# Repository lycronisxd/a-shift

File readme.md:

# a-shift
## a high-quality sim racing shifter targeted at being as cheap as possible to manufacture.

\

### pcb and schematic

### bill of materials

﻿ Item No. | Part No. | Part Name | Qty. | Supplier | Unit Cost | Total Cost |
|---|---|---|---|---|---|---|
| 1 | 3D-001 | 3d printed y-axis chamber | 1 | 3d printing service / at home printing | N/A | N/A |
| 2 | 3D-002 | 3d printed x-axis bearing peg | 2 | 3d printing service / at home printing | N/A | N/A |
| 3 | 3D-003 | 3d printed y-axis bearing peg | 1 | 3d printing service / at home printing | N/A | N/A |
| 4 | 3D-004 | 3d printed main chassis | 1 | 3d printing service / at home printing | N/A | N/A |
| 5 | 3D-005 | 3d printed shift gate | 1 | 3d printing service / at home printing | N/A | N/A |
| 6 | 3D-006 | 3d printed y-axis bearing holder | 1 | 3d printing service / at home printing | N/A | N/A |
| 7 | 3D-007 | 3d printed shift knob | 1 | 3d printing service / at home printing | N/A | N/A |
| 8 | 3D-008 | 3d printed clamp head | 1 | 3d printing service / at home printing | N/A | N/A |
| 9 | 3D-009 | 3d printed clamp body | 1 | 3d printing service / at home printing | N/A | N/A |
| 10 | BR-001 | 608 series bearing | 4 | aliexpress | £0.44 | £4.35 (10pcs) |
| 11 | BR-002 | 625 series bearing | 2 | aliexpress | £0.37 | £3.68 (10pcs) |
| 12 | MNT-001 | m3x5mm bolt | 4 | accu | £0.27 | £1.08 |
| 13 | MNT-002 | m4 nut | 8 | accu | £0.18 | £1.44 |
| 14 | MNT-003 | m6 washers | 8 | accu | £0.19 | £1.52 |
| 15 | MNT-004 | m4x10mm bolt | 15 | accu | £0.15 | £2.25 |
| 16 | MNT-005 | m5 nut | 2 | accu | £0.43 | £0.86 |
| 17 | MNT-006 | m5x10mm bolt | 2 | accu | £0.49 | £0.98 |
| 18 | MNT-007 | m10 washer | 1 | accu | £0.82 | £0.82 |
| 19 | MNT-008 | m10 nut | 1 | accu | £1.01 | £1.01 |
| 20 | SPR-001 | 25mm long, 5mm diameter springs | 2 | aliexpress | £0.29 | £2.89 (10pcs) |
| 21 | SPR-002 | 45mm long, 5mm diameter springs | 2 | aliexpress | £0.37 | £3.73 (10pcs) |
| 22 | SPR-003 | 20mm long, 11mm diameter spring | 1 | aliexpress | £0.26 | £2.59 (10pcs) |
| 23 | MSC-001 | 200mm m10 threaded rod | 1 | aliexpress | £4.31 | £4.31 |
| 24 | MSC-002 | kw13-2 limit switches | 8 | aliexpress | £0.16 | £1.63 |
| 25 | PCB-001 | a-shift pcb (if assembled, ignore the following parts) | 1 | jlcpcb with gerber files | £4 | £4 |
| 26 | PCB-002 | CL21B105KBFNNNG 1uF capacitor | 1 | digikey | £0.09 | £0.09 |
| 27 | PCB-003 | CL21C220JBANNNC 22pF capacitor | 2 | digikey | £0.08 | £0.16 |
| 28 | PCB-004 | CL21B104KBCNNNC 0.1uF capacitor | 4 | digikey | £0.08 | £0.32 |
| 29 | PCB-005 | 1050170001 micro usb connector | 1 | digikey | £0.70 | £0.70 |
| 30 | PCB-006 | RC0805FR-0710KL 10k ohm resistor | 1 | digikey | £0.08 | £0.08 |
| 31 | PCB-007 | RC0805FR-0722RL 22 ohm resistor | 2 | digikey | £0.08 | £0.16 |
| 32 | PCB-008 | 1825910-6 tactile switch | 1 | digikey | £0.10 | £0.10 |
| 33 | PCB-009 | ATMEGA32U4-AU microcontroller | 1 | digikey | £4.01 | £4.01 |
| 34 | PCB-010 | ABM3-16.000MHZ-D2Y-T 16mhz crystal oscillator | 1 | digikey | £0.42 | £0.42 |\

total price (excl. 3d printing services, shipping and tax), <b>£43.18 (~60 USD)</b>

### relevant links
link to **public onshape project**:
<a href="https://cad.onshape.com/documents/ae479125a780254f271543a6/w/35b4ca05e55e778462ce5fb0/e/28c8145b059bf4585cd308b0"> click this </a>

link to **3d printed parts**:
<a href="https://www.thingiverse.com/thing:7376293">click here!</a>

### features
<ul>
<li>custom designed pcb based on the atmega32u4 for ease of future designing :)</li>
<li>7+R normally</li>
<li>5+R capability</li>
<li>sequential shifter capability</li>
<li>built in clamping system for tables or sim rigs</li>
</ul>

### how it works
<ul>
<li>uses a combination of software and hardware to be used as a shifter in racing or driving games</li>
<li>the used limit switches are mapped as controller buttons inside of game settings</li>
<li>can use the shifter sequentially if printing the sequential shift gate and using rubber bands!</li>
</ul>

### instructions
<a href="https://github.com/lycronisxd/a-shift/blob/main/instructions.md">click here!</a>

### credits + ai declaration
<a href="https://www.youtube.com/@amstudioprojects">amstudio</a> for <a href="https://www.youtube.com/watch?v=YMD8e26s7VE&t=88s">this video</a>\
about <a href="https://www.thingiverse.com/Noctiluxx/designs">noctiluxx's <a href="https://www.thingiverse.com/thing:1274947">h-pattern shifter design</a> for the forwards and backwards action of the shifter being locked <3 

i used google gemini to understand why the length of the shift lever mattered\
i used chatgpt to confirm the selection of the electronic components that i plan to use for the pcb (capacitors, resistors etc.)

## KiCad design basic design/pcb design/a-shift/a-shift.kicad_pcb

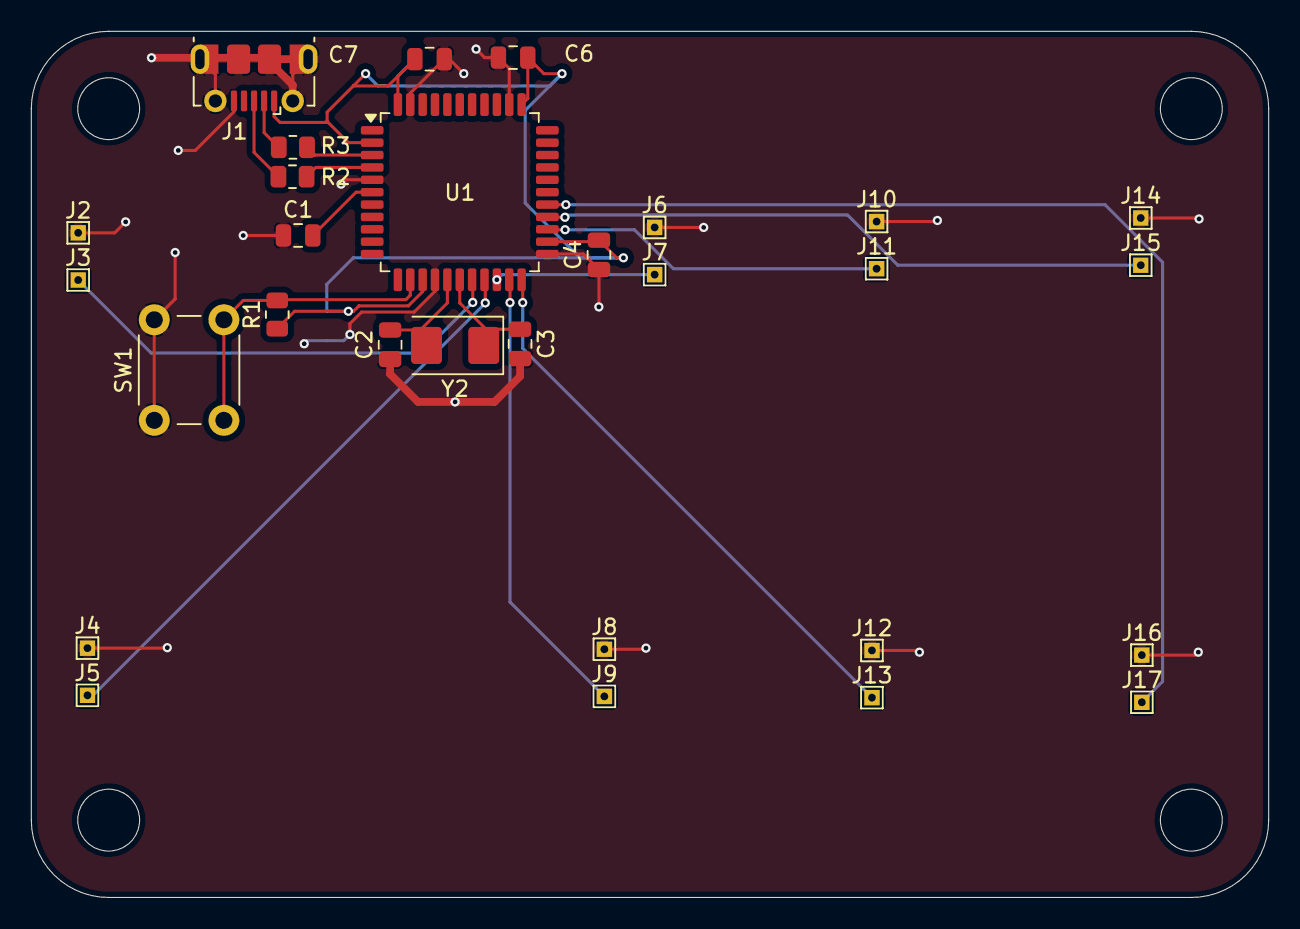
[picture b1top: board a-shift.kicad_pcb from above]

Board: 2 copper layers, 80.0 x 56.0 mm, 30 parts (1 on the bottom side), 18 nets.

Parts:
C1: 1uF; C_0805_2012Metric
C2, C3: 22pF; C_0805_2012Metric
C4, C5, C6, C7: 0.1uF; C_0805_2012Metric
J1: USB_B_Micro; USB_Micro-B_Molex-105017-0001
J2: GND1; TestPoint_THTPad_1.0x1.0mm_Drill0.5mm
J3: PD0; TestPoint_THTPad_1.0x1.0mm_Drill0.5mm
J4: GND2; TestPoint_THTPad_1.0x1.0mm_Drill0.5mm
J5: PD1; TestPoint_THTPad_1.0x1.0mm_Drill0.5mm
J6: GND3; TestPoint_THTPad_1.0x1.0mm_Drill0.5mm
J7: PD2; TestPoint_THTPad_1.0x1.0mm_Drill0.5mm
J8: GND4; TestPoint_THTPad_1.0x1.0mm_Drill0.5mm
J9: PD3; TestPoint_THTPad_1.0x1.0mm_Drill0.5mm
J10: GND5; TestPoint_THTPad_1.0x1.0mm_Drill0.5mm
J11: PD4; TestPoint_THTPad_1.0x1.0mm_Drill0.5mm
J12: GND6; TestPoint_THTPad_1.0x1.0mm_Drill0.5mm
J13: PD5; TestPoint_THTPad_1.0x1.0mm_Drill0.5mm
J14: GND7; TestPoint_THTPad_1.0x1.0mm_Drill0.5mm
J15: PD6; TestPoint_THTPad_1.0x1.0mm_Drill0.5mm
J16: GND8; TestPoint_THTPad_1.0x1.0mm_Drill0.5mm
J17: PD7; TestPoint_THTPad_1.0x1.0mm_Drill0.5mm
R1: 10k; R_0805_2012Metric
R2, R3: 22; R_0805_2012Metric
SW1: SW_Push; SW_PUSH_6mm
U1: ATmega32U4-A; TQFP-44_10x10mm_P0.8mm
Y2: Crystal_GND3_Small; Crystal_SMD_5032-2Pin_5.0x3.2mm

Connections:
+5V: C4.2, C5.2, C6.2, C7.2, J1.1 (VBUS), R1.1, U1.2 (UVCC), U1.14 (VCC), U1.24 (AVCC), U1.34 (VCC), U1.44 (AVCC)
/PD0: J3.1 (Pin_1_1), U1.18 (PD0)
/PD1: J5.1 (Pin_1_1), U1.19 (PD1)
/PD2: J7.1 (Pin_1_1), U1.20 (PD2)
/PD3: J9.1 (Pin_1_1), U1.21 (PD3)
/PD4: J11.1 (Pin_1_1), U1.25 (PD4)
/PD5: J13.1 (Pin_1_1), U1.22 (PD5)
/PD6: J15.1 (Pin_1_1), U1.26 (PD6)
/PD7: J17.1 (Pin_1_1), U1.27 (PD7)
/d+: J1.3 (D+), R2.1
/d-: J1.2 (D-), R3.1
GND: C1.1, C2.1, C3.2, C4.1, C5.1, C6.1, C7.1, J1.5 (GND), J1.SH (Shield), J2.1 (Pin_1_1), J4.1 (Pin_1_1), J6.1 (Pin_1_1), J8.1 (Pin_1_1), J10.1 (Pin_1_1), J12.1 (Pin_1_1), J14.1 (Pin_1_1), J16.1 (Pin_1_1), SW1.1, U1.5 (UGND), U1.15 (GND), U1.23 (GND), U1.35 (GND), U1.43 (GND)
unnamed: R2.2, U1.4 (D+)
unnamed: R3.2, U1.3 (D-)
unnamed: C1.2, U1.6 (UCAP)
unnamed: C3.1, U1.17 (XTAL1), Y2.1
unnamed: C2.2, U1.16 (XTAL2), Y2.2
unnamed: R1.2, SW1.2, U1.13 (~RESET)

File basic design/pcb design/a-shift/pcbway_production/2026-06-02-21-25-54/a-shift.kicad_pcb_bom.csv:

Designator,Quantity,Value,Footprint,Package,MPN,DNP,Mount_Type,Description,KiLib_Generator
C1,1,1uF,C_0805_2012Metric,,,,smt,"Unpolarized capacitor, small symbol",SMD_2terminal_chip_molded
"C2, C3",2,22pF,C_0805_2012Metric,,,,smt,"Unpolarized capacitor, small symbol",SMD_2terminal_chip_molded
"C4, C5, C6, C7",4,0.1uF,C_0805_2012Metric,,,,smt,"Unpolarized capacitor, small symbol",SMD_2terminal_chip_molded
J1,1,USB_B_Micro,USB_Micro-B_Molex-105017-0001,,,,smt,USB Micro Type B connector,
J10,1,GND5,TestPoint_THTPad_1.0x1.0mm_Drill0.5mm,,,,tht,"Generic connector, single row, 01x01, script generated (kicad-library-utils/schlib/autogen/connector/)",
J11,1,PD4,TestPoint_THTPad_1.0x1.0mm_Drill0.5mm,,,,tht,"Generic connector, single row, 01x01, script generated (kicad-library-utils/schlib/autogen/connector/)",
J12,1,GND6,TestPoint_THTPad_1.0x1.0mm_Drill0.5mm,,,,tht,"Generic connector, single row, 01x01, script generated (kicad-library-utils/schlib/autogen/connector/)",
J13,1,PD5,TestPoint_THTPad_1.0x1.0mm_Drill0.5mm,,,,tht,"Generic connector, single row, 01x01, script generated (kicad-library-utils/schlib/autogen/connector/)",
J14,1,GND7,TestPoint_THTPad_1.0x1.0mm_Drill0.5mm,,,,tht,"Generic connector, single row, 01x01, script generated (kicad-library-utils/schlib/autogen/connector/)",
J15,1,PD6,TestPoint_THTPad_1.0x1.0mm_Drill0.5mm,,,,tht,"Generic connector, single row, 01x01, script generated (kicad-library-utils/schlib/autogen/connector/)",
J16,1,GND8,TestPoint_THTPad_1.0x1.0mm_Drill0.5mm,,,,tht,"Generic connector, single row, 01x01, script generated (kicad-library-utils/schlib/autogen/connector/)",
J17,1,PD7,TestPoint_THTPad_1.0x1.0mm_Drill0.5mm,,,,tht,"Generic connector, single row, 01x01, script generated (kicad-library-utils/schlib/autogen/connector/)",
J2,1,GND1,TestPoint_THTPad_1.0x1.0mm_Drill0.5mm,,,,tht,"Generic connector, single row, 01x01, script generated (kicad-library-utils/schlib/autogen/connector/)",
J3,1,PD0,TestPoint_THTPad_1.0x1.0mm_Drill0.5mm,,,,tht,"Generic connector, single row, 01x01, script generated (kicad-library-utils/schlib/autogen/connector/)",
J4,1,GND2,TestPoint_THTPad_1.0x1.0mm_Drill0.5mm,,,,tht,"Generic connector, single row, 01x01, script generated (kicad-library-utils/schlib/autogen/connector/)",
J5,1,PD1,TestPoint_THTPad_1.0x1.0mm_Drill0.5mm,,,,tht,"Generic connector, single row, 01x01, script generated (kicad-library-utils/schlib/autogen/connector/)",
J6,1,GND3,TestPoint_THTPad_1.0x1.0mm_Drill0.5mm,,,,tht,"Generic connector, single row, 01x01, script generated (kicad-library-utils/schlib/autogen/connector/)",
J7,1,PD2,TestPoint_THTPad_1.0x1.0mm_Drill0.5mm,,,,tht,"Generic connector, single row, 01x01, script generated (kicad-library-utils/schlib/autogen/connector/)",
J8,1,GND4,TestPoint_THTPad_1.0x1.0mm_Drill0.5mm,,,,tht,"Generic connector, single row, 01x01, script generated (kicad-library-utils/schlib/autogen/connector/)",
J9,1,PD3,TestPoint_THTPad_1.0x1.0mm_Drill0.5mm,,,,tht,"Generic connector, single row, 01x01, script generated (kicad-library-utils/schlib/autogen/connector/)",
R1,1,10k,R_0805_2012Metric,,,,smt,"Resistor, small symbol",SMD_2terminal_chip_molded
"R2, R3",2,22,R_0805_2012Metric,,,,smt,"Resistor, small symbol",SMD_2terminal_chip_molded
SW1,1,SW_Push,SW_PUSH_6mm,,,,tht,"Push button switch, generic, two pins",
U1,1,ATmega32U4-A,TQFP-44_10x10mm_P0.8mm,,,,smt,"16MHz, 32kB Flash, 2.5kB SRAM, 1kB EEPROM, USB 2.0, TQFP-44",package/gullwing
Y2,1,Crystal_GND3_Small,Crystal_SMD_5032-2Pin_5.0x3.2mm,,,,smt,"Three pin crystal, GND on pin 3, small symbol",crystal_resonator_oscillator

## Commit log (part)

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2026-06-01 created a shift layout for the first revision of the shifter in excalidraw/obsidian
2026-06-01 finished the first revision of the shift plate and lever design
2026-06-02 started design of the rotation mechanism
2026-06-02 finished basic rotation mechanism design documentation
2026-06-02 started and finished the centering mechanism design for iteration 1
2026-06-02 started the designing of the tactile feedback mechanism for iteration 1
2026-06-02 finished all the mechanisms and added colour to my 3d model
2026-06-02 design and route a main pcb for the shifter
2026-06-02 create production files for the 1st pcb
2026-06-03 add an image of the mechanism and circuit board to the repo
2026-06-03 create a readme file
2026-06-03 update the readme with a frame of what to put where
2026-06-04 update readme.md for style
2026-06-18 add pcb components link to instructions.md
2026-06-29 finish text instructions in instructions.md
2026-06-29 update readme.md with thingiverse link
